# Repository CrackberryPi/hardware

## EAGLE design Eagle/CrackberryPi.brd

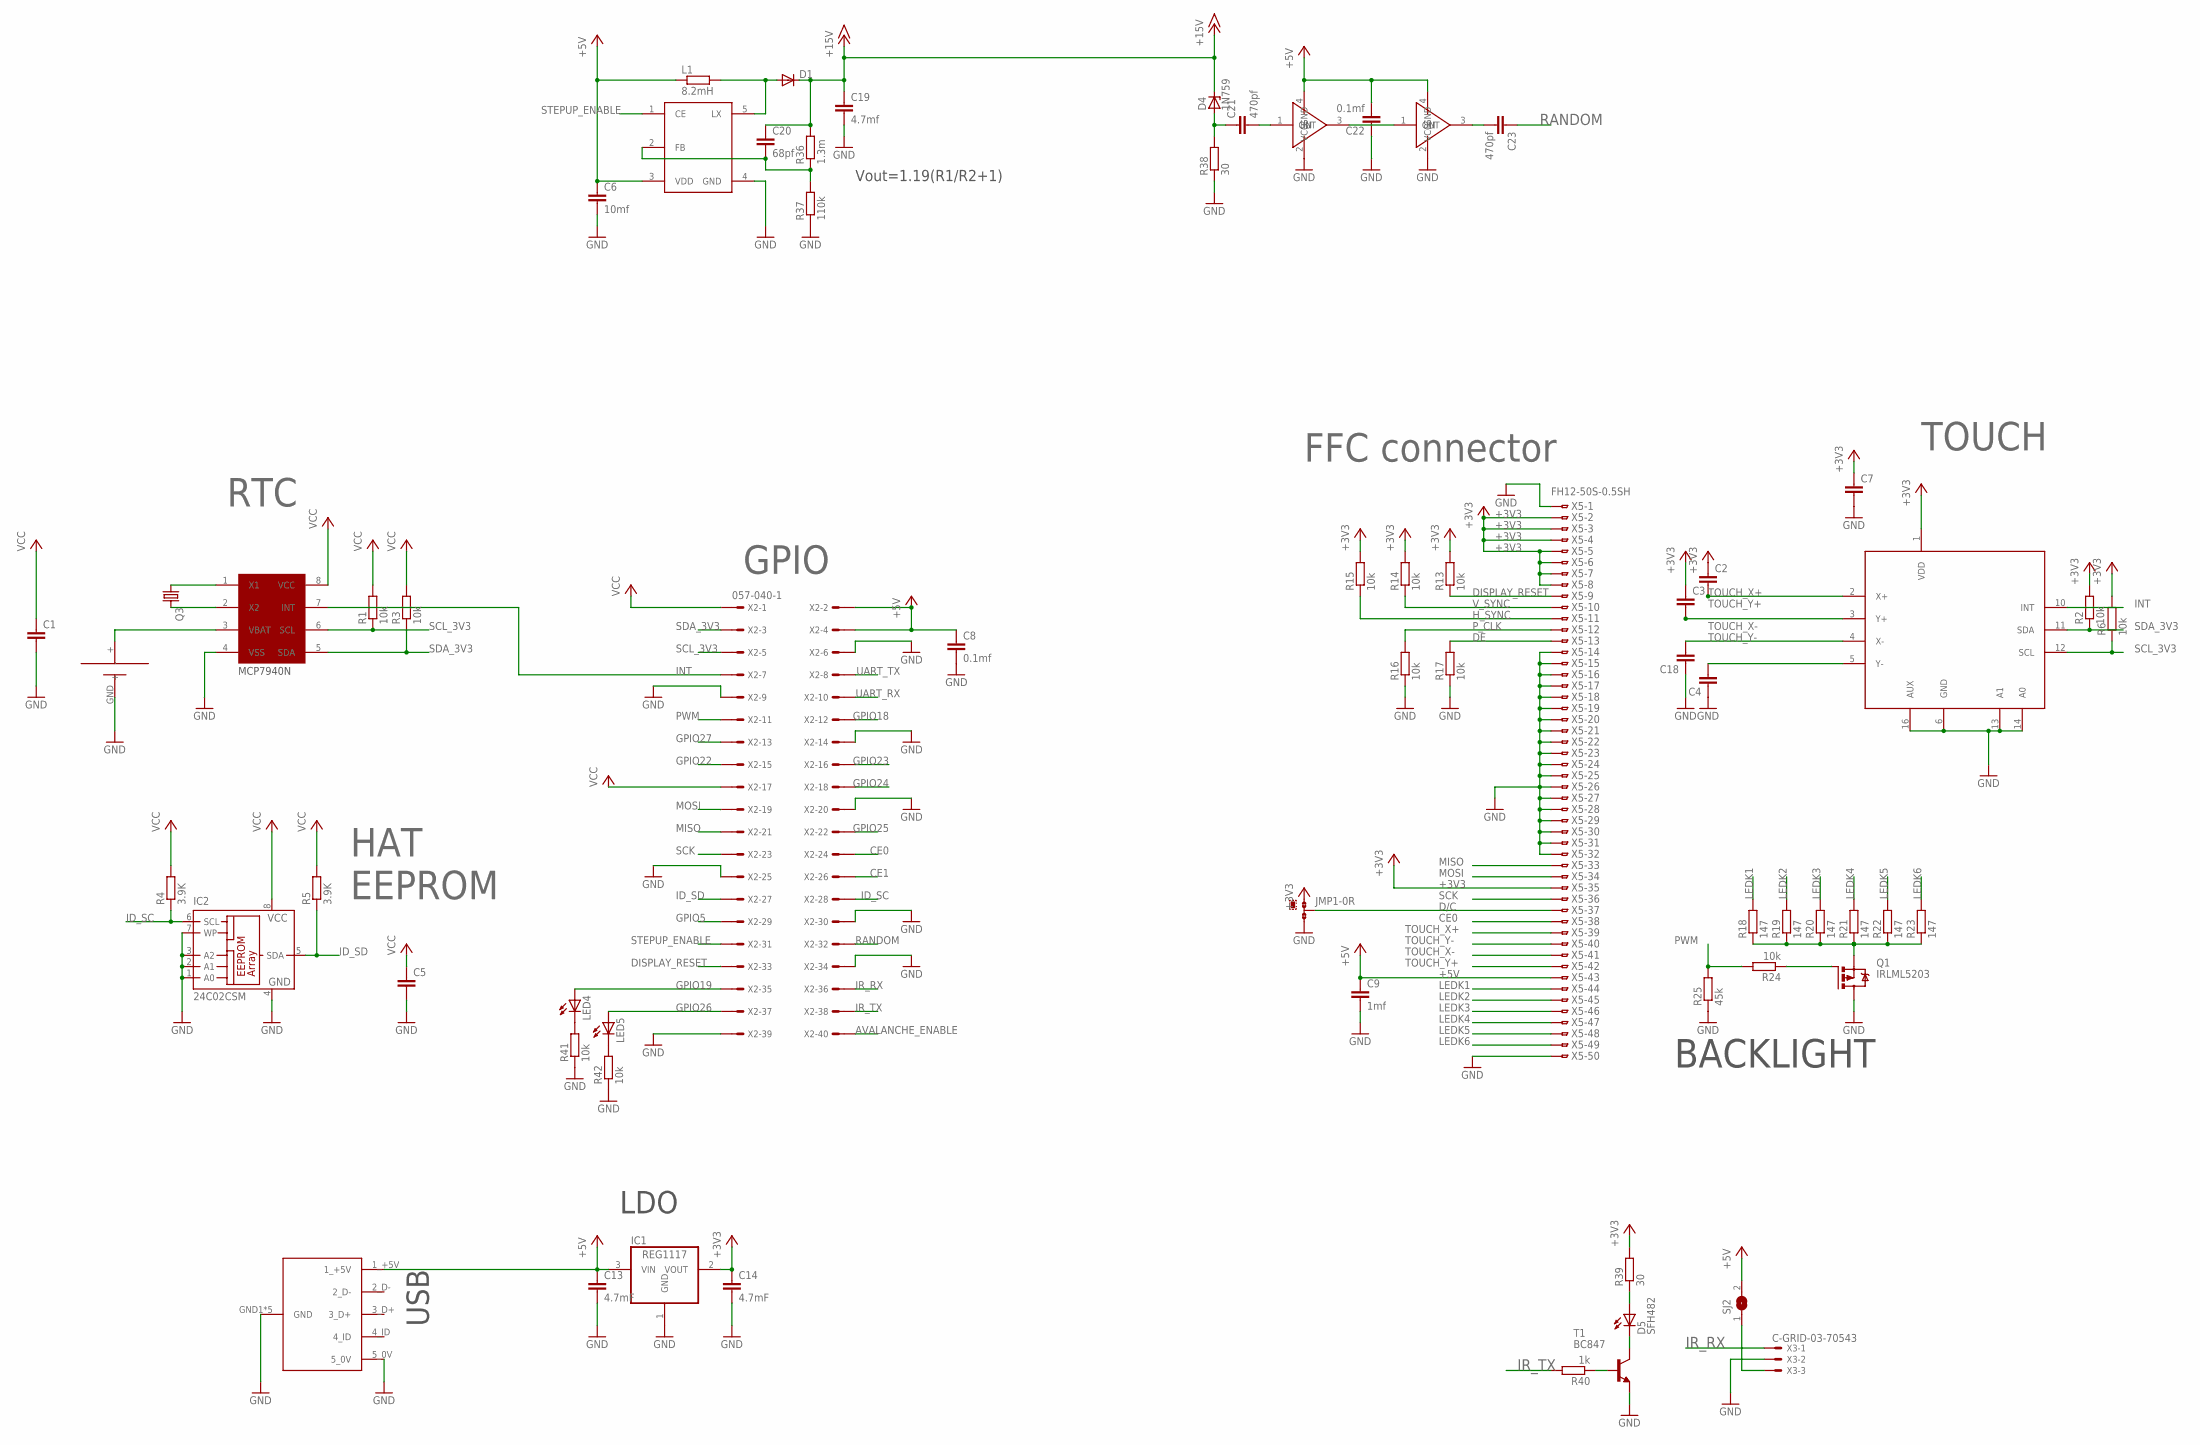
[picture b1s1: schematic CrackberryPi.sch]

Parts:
C1, C2, C3, C4, C5, C7, C18: C-EUC0603; C0603
C6: 10mf; C0603
C8, C22: 0.1mf; C0603
C9: 1mf; C0603
C13, C14: 4.7mF; C0603
C19: 4.7mf; C0603
C20: 68pf; C0603
C21, C23: 470pf; C0603
D1: DIODE-SOD123; SOD123
D4: 1N759; SOD80C
D5: SFH482
IC1: REG1117; SOT223
IC2: 24C02CSM; SO-08M
JMP1: 0R-JUMPC; C0R-JMP
L1: 8.2mH; R1210
LED4, LED5: LED_ESML0603; LED_SML0603
Q1: IRLML5203; MICRO3
Q3: CRYSTALMM20SS; MM20SS
R1, R2, R3, R6, R13, R14, R15, R16, R17, R24, R41, R42: 10k; R0603
R4, R5: 3.9K; R0603
R18, R19, R20, R21, R22, R23: 147; R0603
R25: 45k; R0603
R36: 1.3m; R0603
R37: 110k; R0603
R38, R39: 30; R0603
R40: 1k; R0603
SJ2: SJ
T1: BC847; SOT23
U$2: NCP1406; SOT23-5L
U$3, U$10: MAX2650; SOT143-W
U$4: CR1216
U$5: MCP7940N; SO08
U$6: TSC2007; TSSOP16
U$9: MICRO_USB
X2: 057-040-1
X3: C-GRID-03-70543; 70543-03
X5: FH12-50S-0.5SH

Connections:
+3V3: C2.1, C3.1, C7.1, C14.1, IC1.2 (VOUT), JMP1.1, R2.2, R6.2, R13.2, R14.2, R15.2, R39.2, U$6.1 (VDD), X5.2, X5.3, X5.4, X5.5, X5.6, X5.7, X5.8, X5.35
+5V: C6.1, C8.1, C9.1, C13.1, C22.2, IC1.3 (VIN), L1.1, SJ2.2, U$2.3 (VDD), U$3.4 (VCC), U$9.1_+5V, U$10.4 (VCC), X2.2, X2.4, X5.43
+15V: C19.1, C20.1, D1.C, D4.C, R36.2
AVALANCHE_ENABLE: X2.40
BASE: R40.1, T1.1 (B)
CE0: X2.24, X5.38
CE1: X2.26
COLLECTOR: D5.K (C), T1.3 (C)
D/C: JMP1.2, X5.37
DE: R17.2, X5.13
DISPLAY_RESET: R13.1, X2.33, X5.9
EMITTER: T1.2 (E)
FB: C20.2, R36.1, R37.2, U$2.2 (FB)
GND: C1.2, C4.1, C5.2, C6.2, C7.2, C8.2, C9.2, C13.2, C14.2, C18.1, C19.2, C22.1, IC1.1 (GND), IC2.1 (A0), IC2.2 (A1), IC2.3 (A2), IC2.4 (GND), IC2.7 (WP), JMP1.3, Q1.3 (D), R16.1, R17.1, R25.1, R37.1, R38.1, R41.1, R42.1, U$2.4 (GND), U$3.2 (GND), U$4.GND (-), U$5.4 (VSS), U$6.6 (GND), U$6.13 (A1), U$6.14 (A0), U$6.16 (AUX), U$9.5_0V, U$9.GND1 (GND), U$9.GND2 (GND), U$9.GND5 (GND), U$9.P$1 (GND), U$9.P$7 (GND), U$10.2 (GND), X2.6, X2.9, X2.14, X2.20, X2.25, X2.30, X2.34, X2.39, X3.2, X5.1, X5.14, X5.15, X5.16, X5.17, X5.18, X5.19, X5.20, X5.21, X5.22, X5.23, X5.24, X5.25, X5.26, X5.27, X5.28, X5.29, X5.30, X5.31, X5.32, X5.50
GPIO5: X2.29
GPIO18: X2.12
GPIO19: LED4.A, X2.35
GPIO22: X2.15
GPIO23: X2.16
GPIO24: X2.18
GPIO25: X2.22
GPIO26: LED5.A, X2.37
GPIO27: X2.13
H_SYNC: R15.1, X5.11
ID_SC: IC2.6 (SCL), R4.1, X2.28
ID_SD: IC2.5 (SDA), R5.1, X2.27
INT: U$5.7 (INT), U$6.10 (INT), X2.7
IN_1: C21.2, U$3.1 (IN)
IR_RX: X2.36, X3.1
IR_TX: R40.2, X2.38
LEDK1: R18.2, X5.44
LEDK2: R19.2, X5.45
LEDK3: R20.2, X5.46
LEDK4: R21.2, X5.47
LEDK5: R22.2, X5.48
LEDK6: R23.2, X5.49
LX: D1.A, L1.2, U$2.5 (LX)
MISO: X2.21, X5.33
MOSI: X2.19, X5.34
unnamed: SJ2.1, X3.3
unnamed: Q1.2 (S), R18.1, R19.1, R20.1, R21.1, R22.1, R23.1
unnamed: C21.1, D4.A, R38.2
unnamed: Q1.1 (G), R24.1
unnamed: D5.A, R39.1
unnamed: LED4.C, R41.2
unnamed: LED5.C, R42.2
OUT1_IN2: U$3.3 (OUT), U$10.1 (IN)
OUT2: C23.2, U$10.3 (OUT)
PWM: R24.2, R25.2, X2.11
P_CLK: R16.2, X5.12
RANDOM: C23.1, X2.32
SCK: X2.23, X5.36
SCL_3V3: R1.1, R6.1, U$5.6 (SCL), U$6.12 (SCL), X2.5
SDA_3V3: R2.1, R3.1, U$5.5 (SDA), U$6.11 (SDA), X2.3
STEPUP_ENABLE: U$2.1 (CE), X2.31
TOUCH_X+: C2.2, U$6.2 (X+), X5.39
TOUCH_X-: C18.2, U$6.4 (X-), X5.41
TOUCH_Y+: C3.2, U$6.3 (Y+), X5.42
TOUCH_Y-: C4.2, U$6.5 (Y-), X5.40
UART_RX: X2.10
UART_TX: X2.8
VBAT+: U$4.+, U$5.3 (VBAT)
VCC: C1.1, C5.1, IC2.8 (VCC), R1.2, R3.2, R4.2, R5.2, U$5.8 (VCC), X2.1, X2.17
V_SYNC: R14.1, X5.10
X1_RTC: Q3.1, U$5.1 (X1)
X2_RTC: Q3.4 (2), U$5.2 (X2)

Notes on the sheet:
RTC
GPIO
HAT EEPROM
TOUCH
FFC connector
BACKLIGHT
MCP7940N
USB
LDO
Vout=1.19(R1/R2+1)

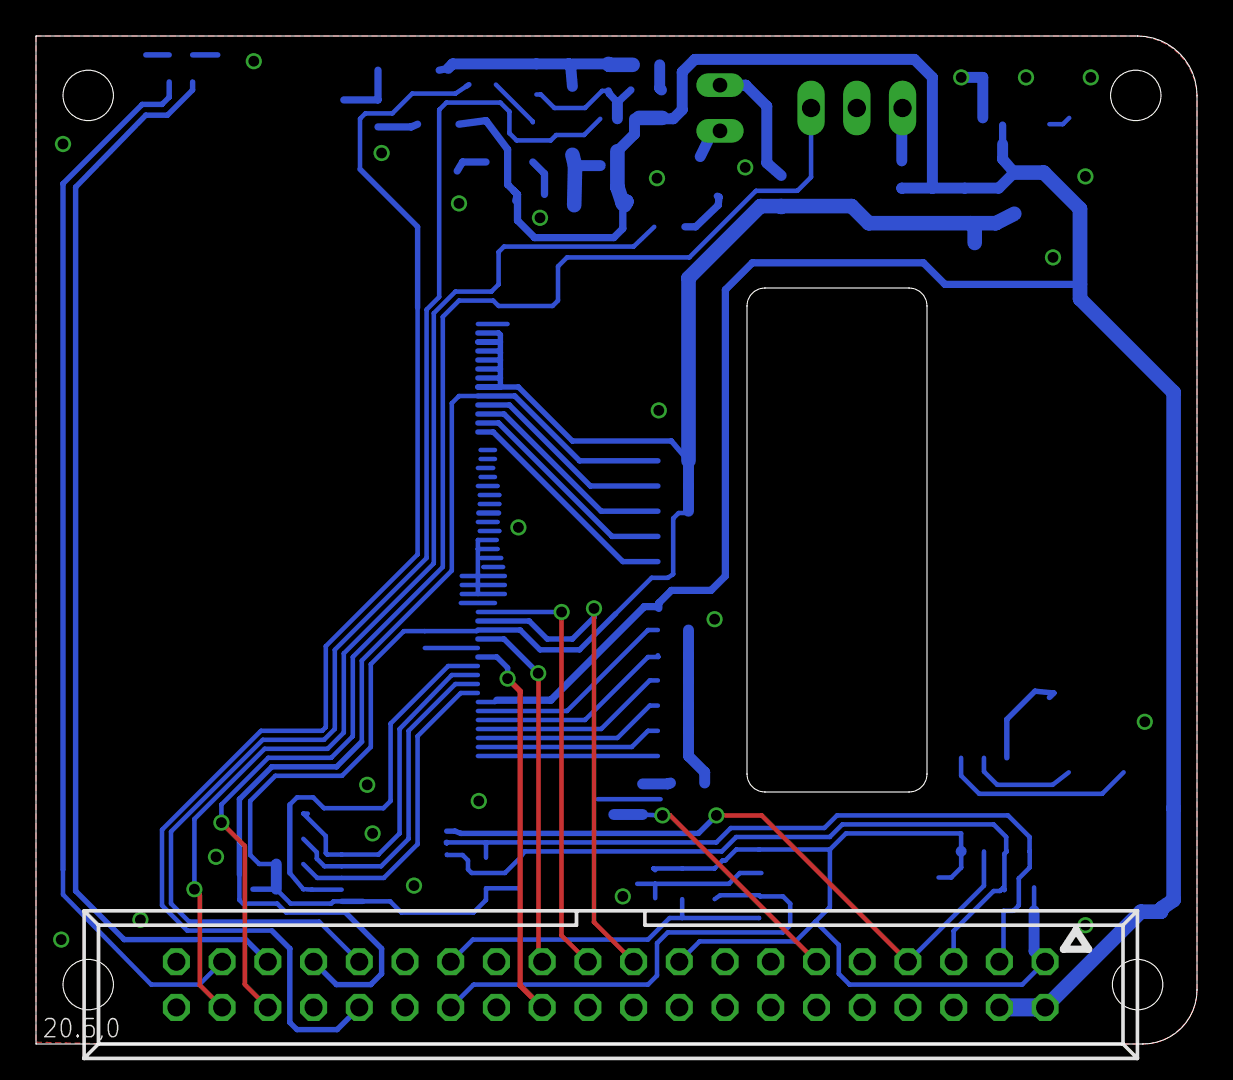
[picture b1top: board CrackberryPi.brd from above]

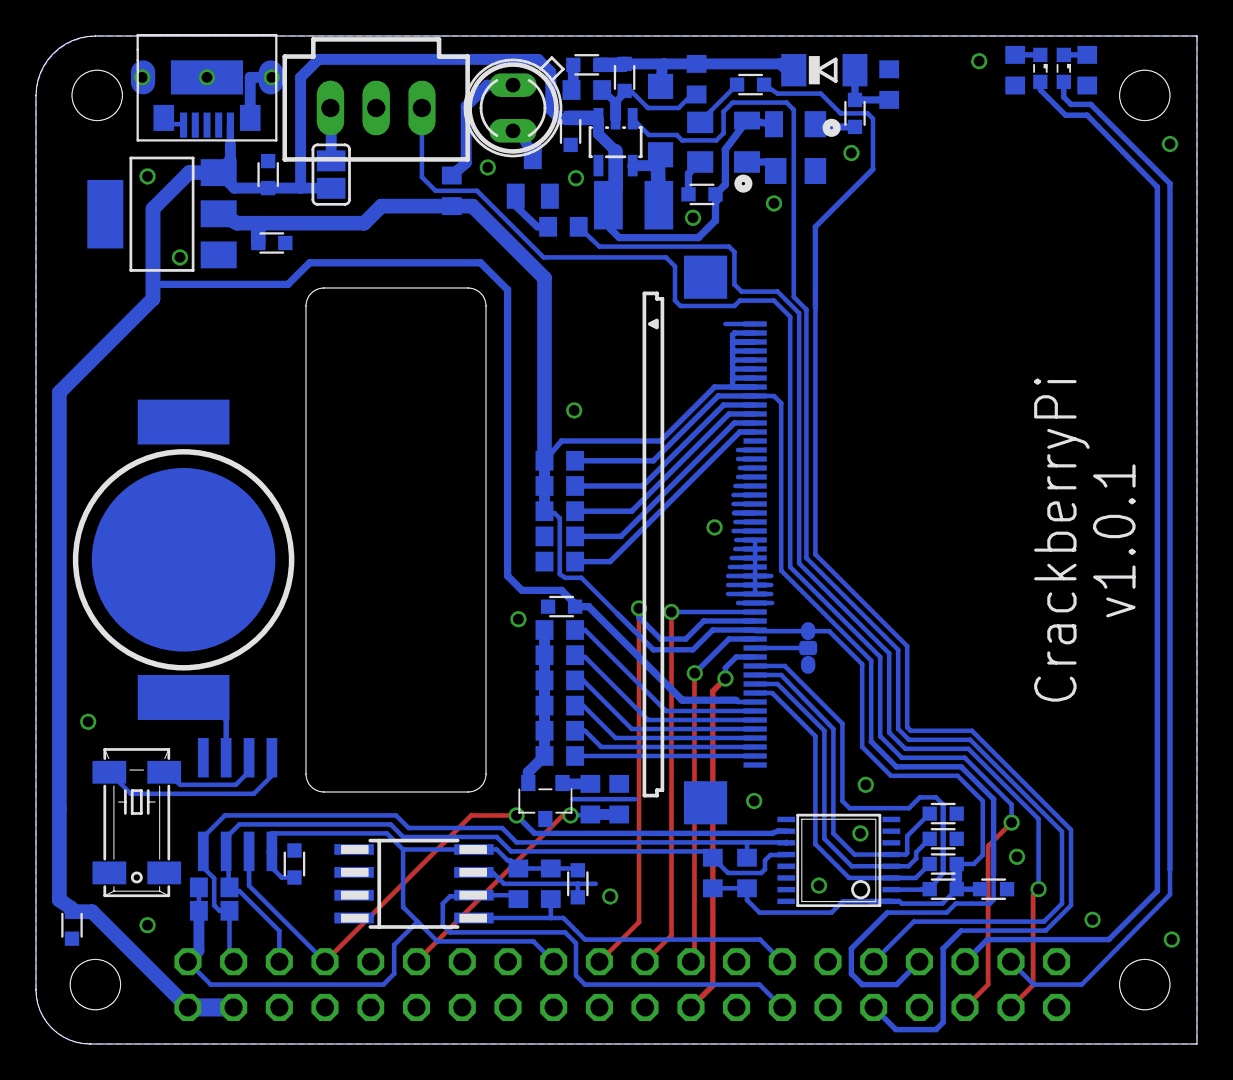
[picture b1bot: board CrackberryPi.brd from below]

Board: 2 copper layers, 64.5 x 56.0 mm, 66 parts (65 on the bottom side), 54 nets.
